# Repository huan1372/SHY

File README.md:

# SHY
Design a smartwatch whose name is SHY.
Planned feature:
Time
Heart rate
Bluetooth
Steps
Calories
Temperature
Timer

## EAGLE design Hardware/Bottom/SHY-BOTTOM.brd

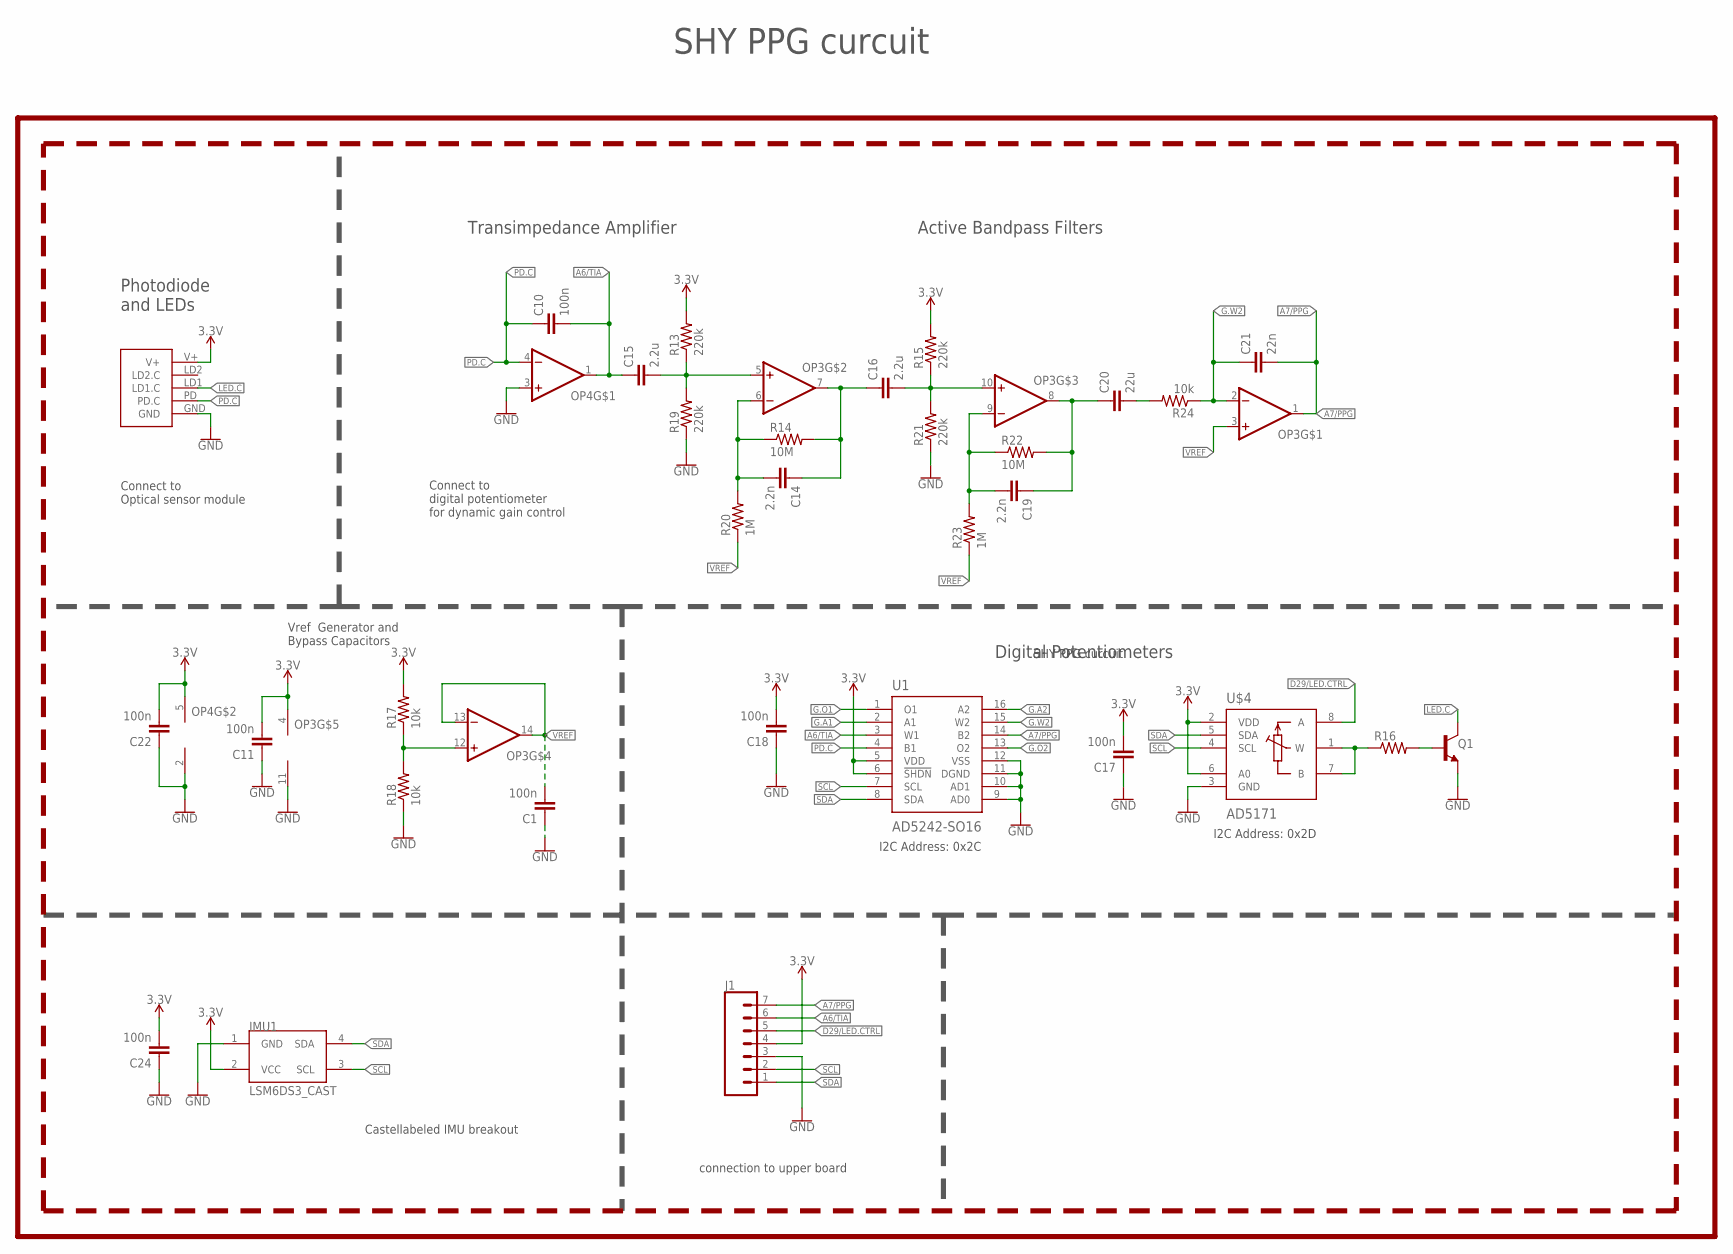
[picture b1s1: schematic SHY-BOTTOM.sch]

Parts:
C1, C10, C11, C17, C18, C22, C24: 100n; C0603
C14, C19: 2.2n; C0603
C15, C16: 2.2u; C0603
C20: 22u; C0603
C21: 22n; C0603
IMU1: LSM6DS3_CAST
J1: CONN_07-1.27MM; 1X07_1.27MM
LOGO1: REVISION.A; REV.A
LOGO2: LINNES.LAB.LOGO
OP3: OP-QUAD-SO14; SO14
OP4: OP-SINGLEOT; SOT23-5
Q1: NPN-GENERIC; SOT23-3
R13, R15, R19, R21: 220k; R0603
R14, R22: 10M; R0603
R16: RESISTOR0603; R0603
R17, R18: 10k; R0402
R20, R23: 1M; R0603
R24: 10k; R0603
U1: AD5242-SO16; SO16
U$3: PPG.MODULE.2
U$4: AD5171; SOT-23-8

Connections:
3.3V: C11.2, C17.2, C18.2, C22.2, C24.2, IMU1.2 (VCC), J1.4, OP3.4 (V+), OP4.5 (V+), R13.2, R15.2, R17.2, U1.5 (VDD), U1.6 (!SHDN), U$3.V+, U$4.2 (VDD), U$4.6 (A0)
A6/TIA: C10.2, C15.1, J1.6, OP4.1 (OUT), U1.3 (W1)
A7/PPG: C21.2, J1.7, OP3.1 (OUT), U1.14 (B2)
D29/LED.CTRL: J1.5, U$4.8 (A)
G.A1: U1.2 (A1)
G.A2: U1.16 (A2)
G.O1: U1.1 (O1)
G.O2: U1.13 (O2)
G.W2: C21.1, OP3.2 (-IN), R24.1, U1.15 (W2)
GND: C1.1, C11.1, C17.1, C18.1, C22.1, C24.1, IMU1.1 (GND), J1.3, OP3.11 (V-), OP4.2 (V-), OP4.3 (+IN), Q1.2 (E), R18.1, R19.1, R21.1, U1.9 (AD0), U1.10 (AD1), U1.11 (DGND), U1.12 (VSS), U$3.GND, U$4.3 (GND)
LED.C: Q1.3 (C), U$3.LD1 (LD1.C)
unnamed: Q1.1 (B), R16.2
unnamed: R16.1, U$4.1 (W), U$4.7 (B)
unnamed: OP3.12 (+IN), R17.1, R18.2
unnamed: C15.2, OP3.5 (+IN), R13.1, R19.2
unnamed: C14.2, OP3.6 (-IN), R14.1, R20.2
unnamed: C14.1, C16.1, OP3.7 (OUT), R14.2
unnamed: C16.2, OP3.10 (+IN), R15.1, R21.2
unnamed: C19.2, OP3.9 (-IN), R22.1, R23.2
unnamed: C19.1, C20.1, OP3.8 (OUT), R22.2
unnamed: C20.2, R24.2
PD.C: C10.1, OP4.4 (-IN), U1.4 (B1), U$3.PD (PD.C)
SCL: IMU1.3 (SCL), J1.2, U1.7 (SCL), U$4.4 (SCL)
SDA: IMU1.4 (SDA), J1.1, U1.8 (SDA), U$4.5 (SDA)
VREF: C1.2, OP3.3 (+IN), OP3.13 (-IN), OP3.14 (OUT), R20.1, R23.1

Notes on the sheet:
Photodiode and LEDs
Active Bandpass Filters
Digital Potentiometers
Transimpedance Amplifier
I2C Address: 0x2C
I2C Address: 0x2D
Connect to Optical sensor module
Connect to digital potentiometer for dynamic gain control
connection to upper board
Castellabeled IMU breakout
Vref Generator and Bypass Capacitors
SHY PPG curcuit

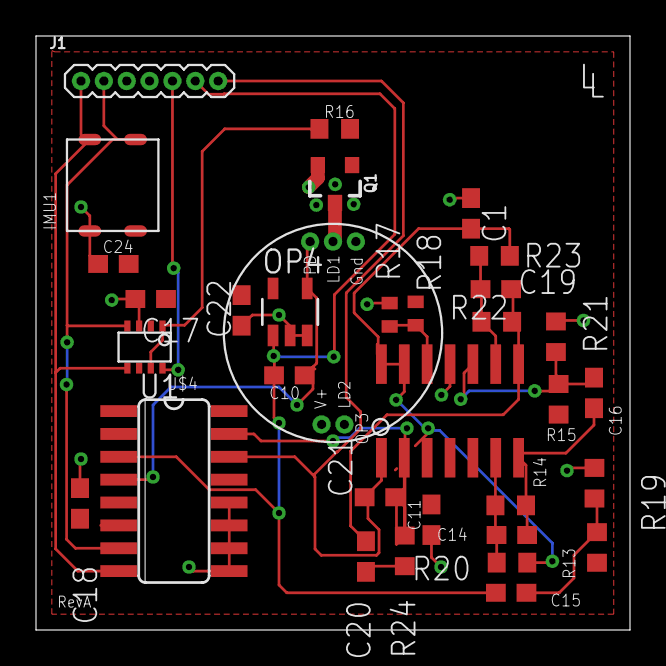
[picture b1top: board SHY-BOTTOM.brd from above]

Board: 2 copper layers, 33.0 x 33.0 mm, 35 parts (0 on the bottom side), 21 nets.

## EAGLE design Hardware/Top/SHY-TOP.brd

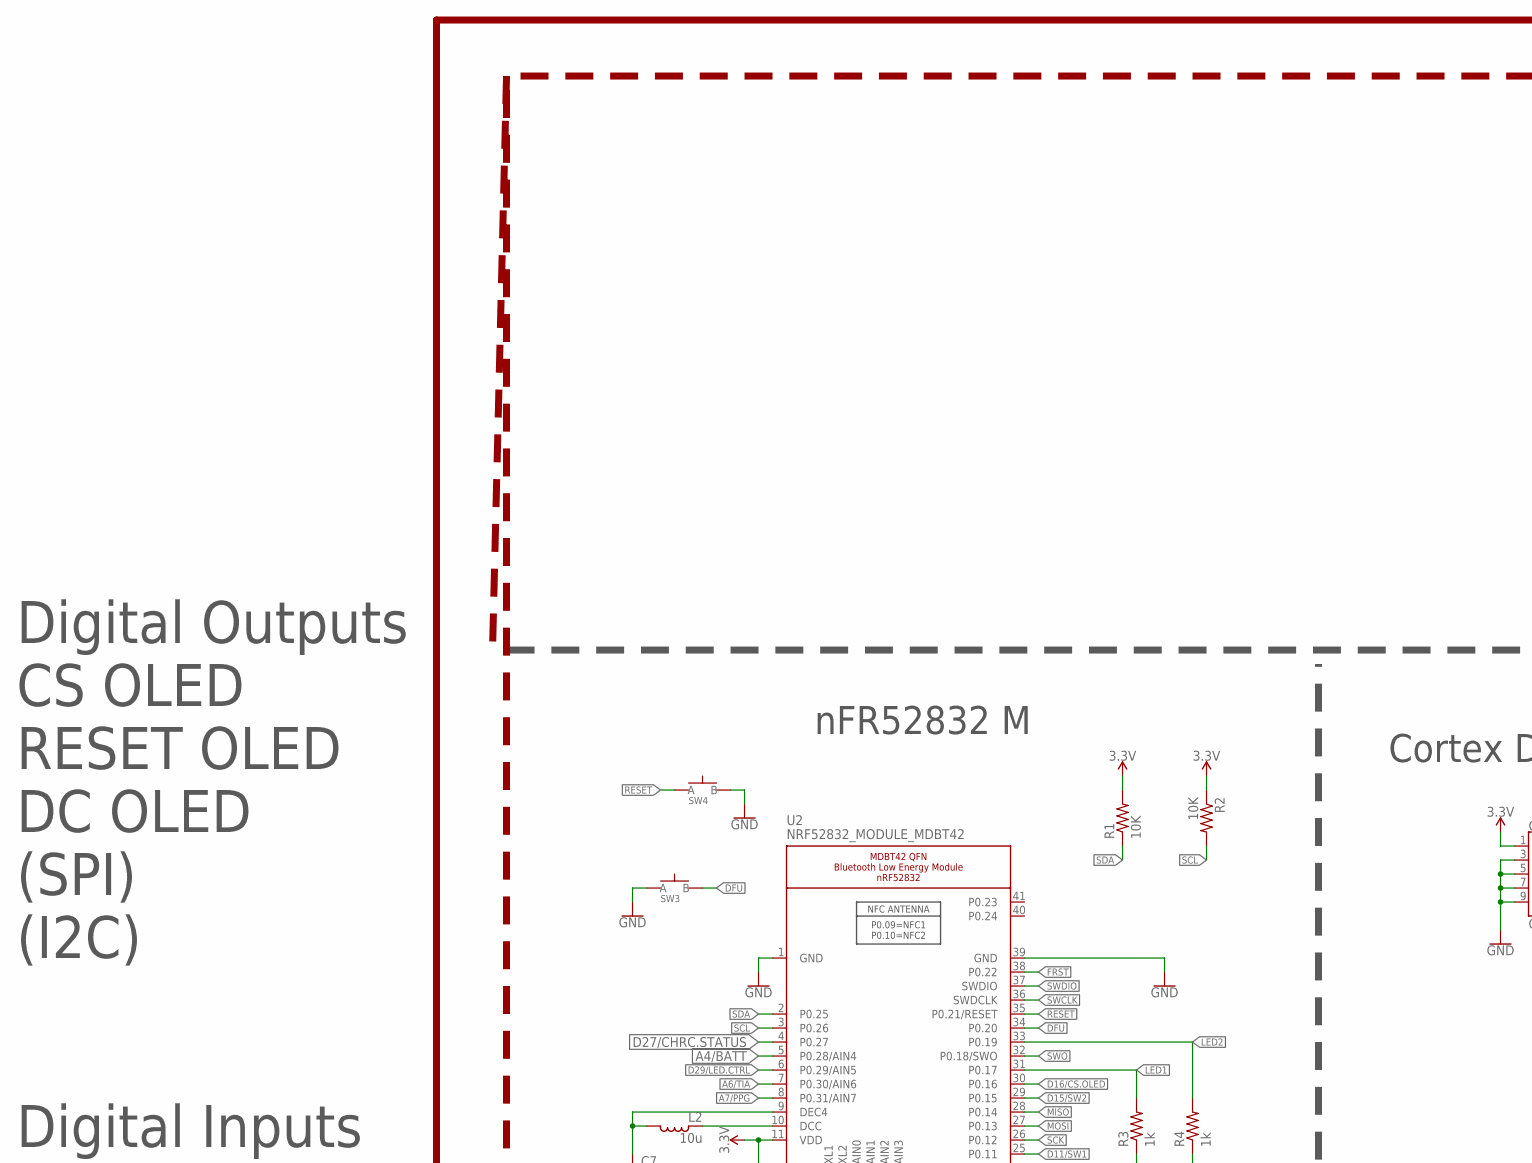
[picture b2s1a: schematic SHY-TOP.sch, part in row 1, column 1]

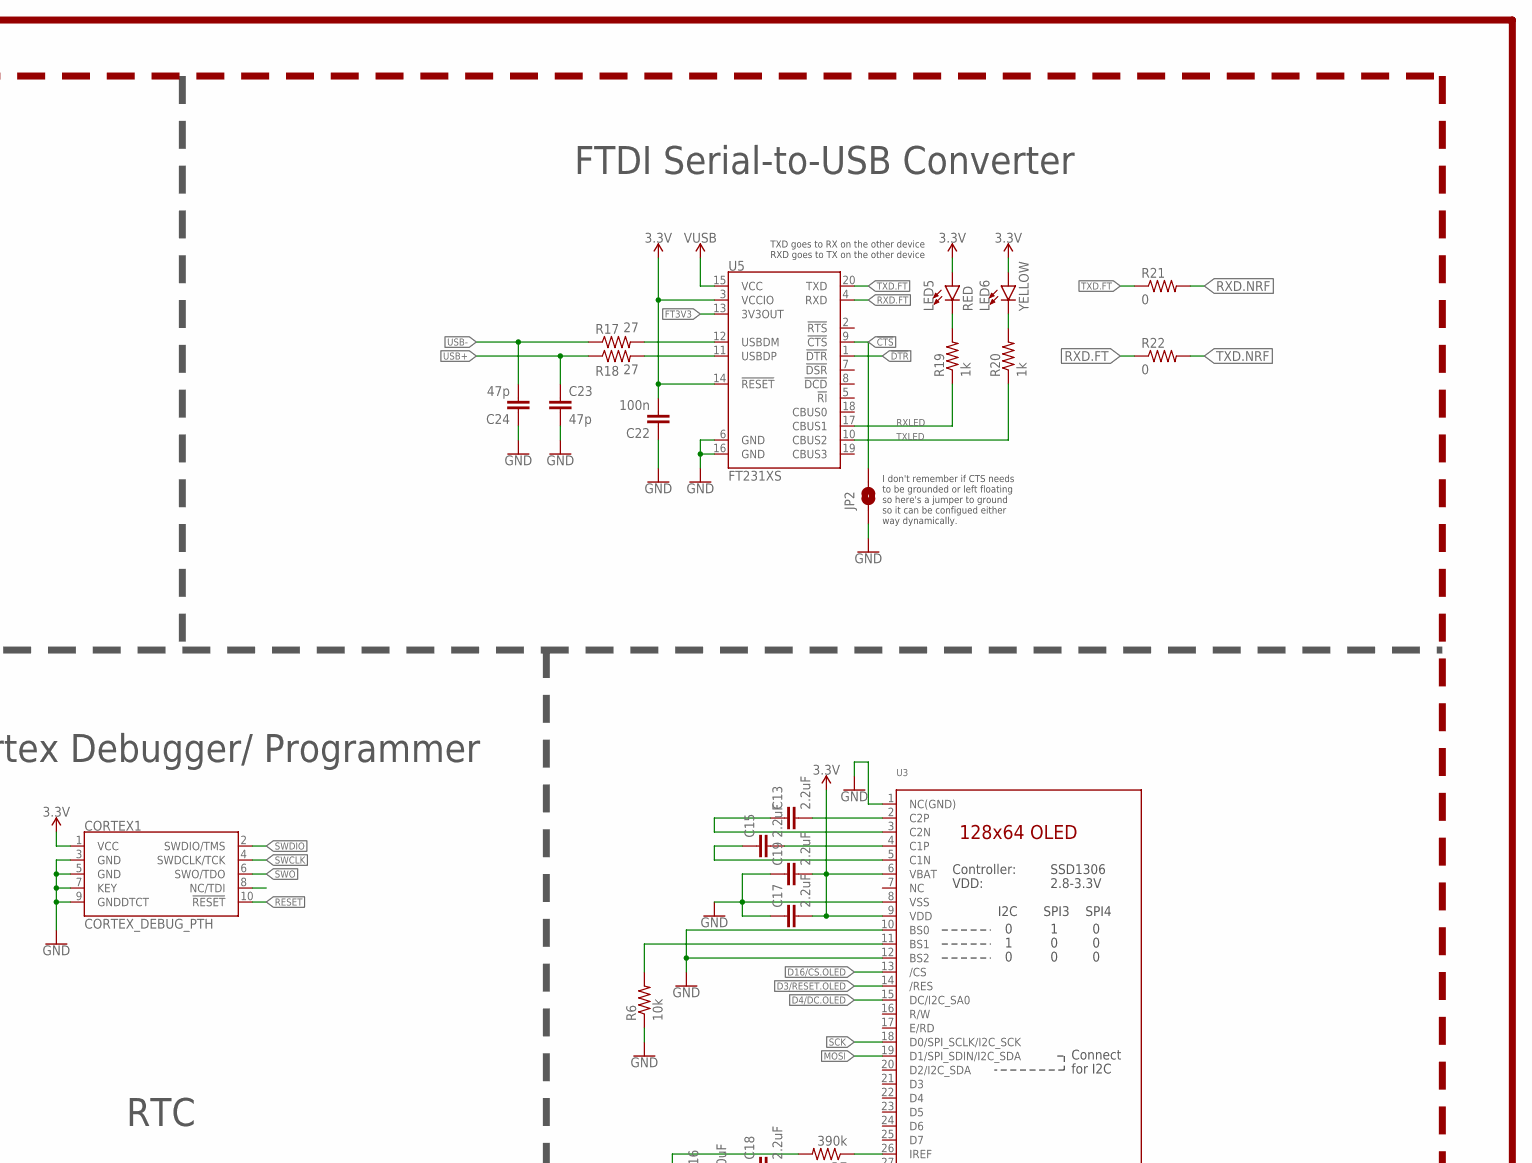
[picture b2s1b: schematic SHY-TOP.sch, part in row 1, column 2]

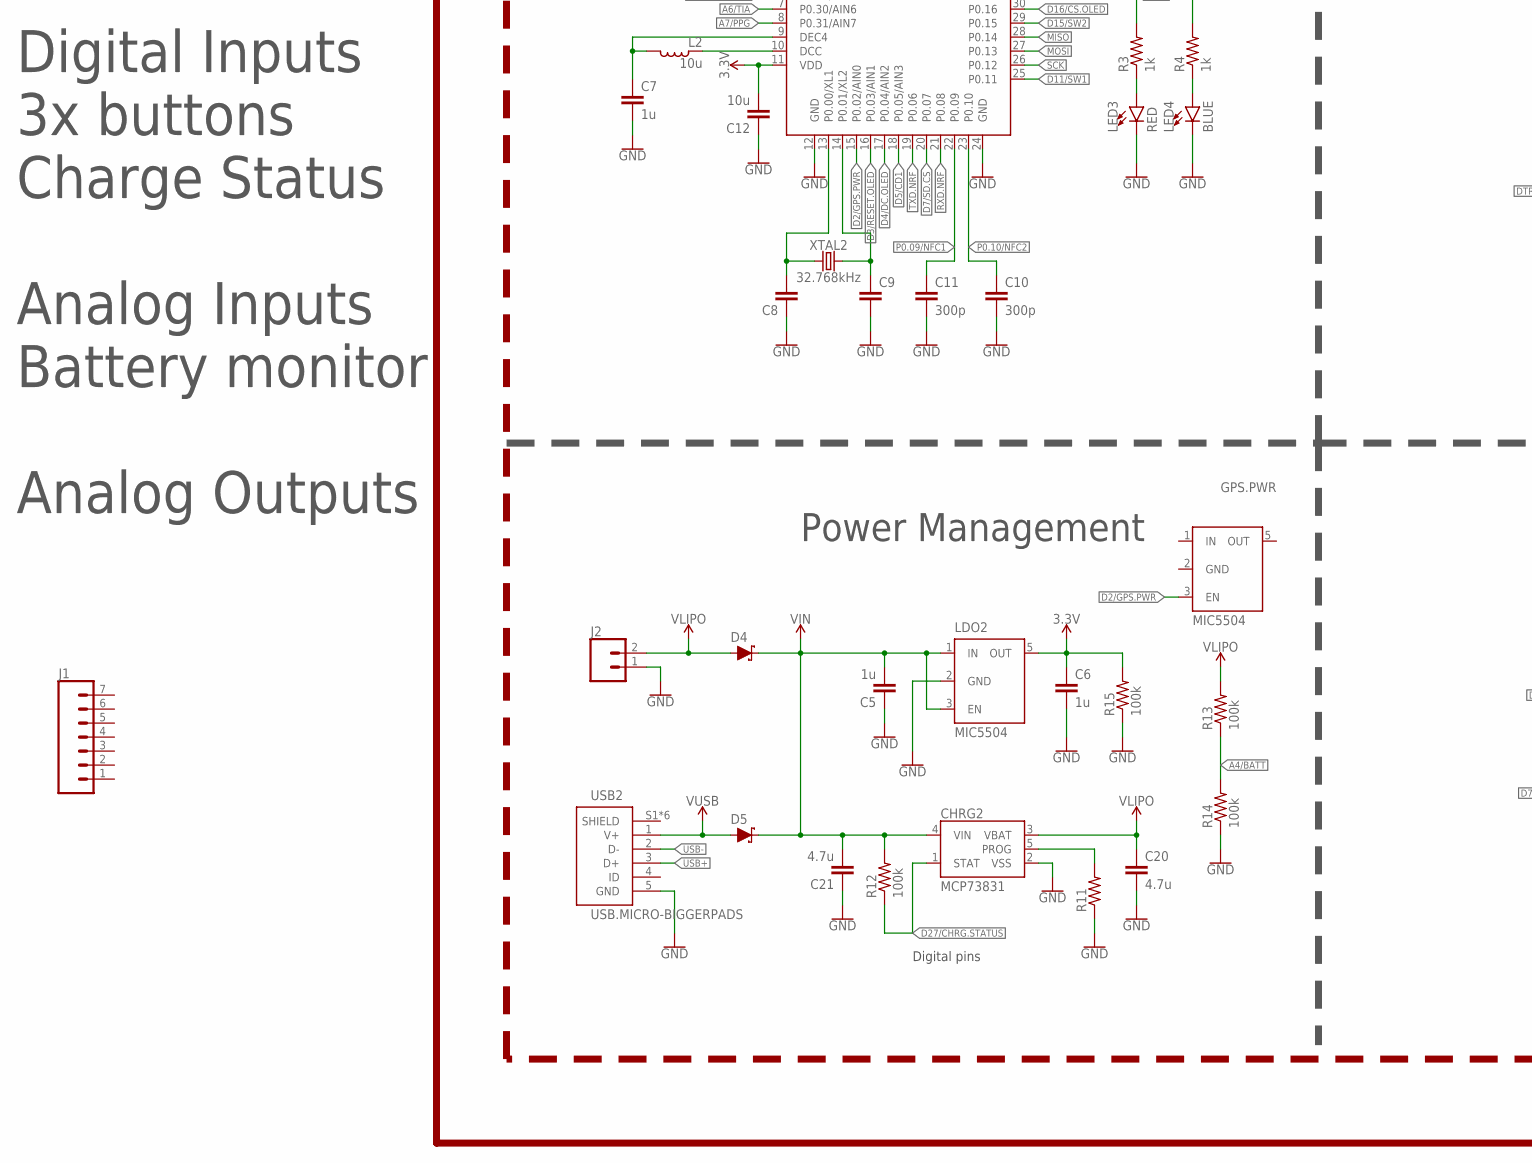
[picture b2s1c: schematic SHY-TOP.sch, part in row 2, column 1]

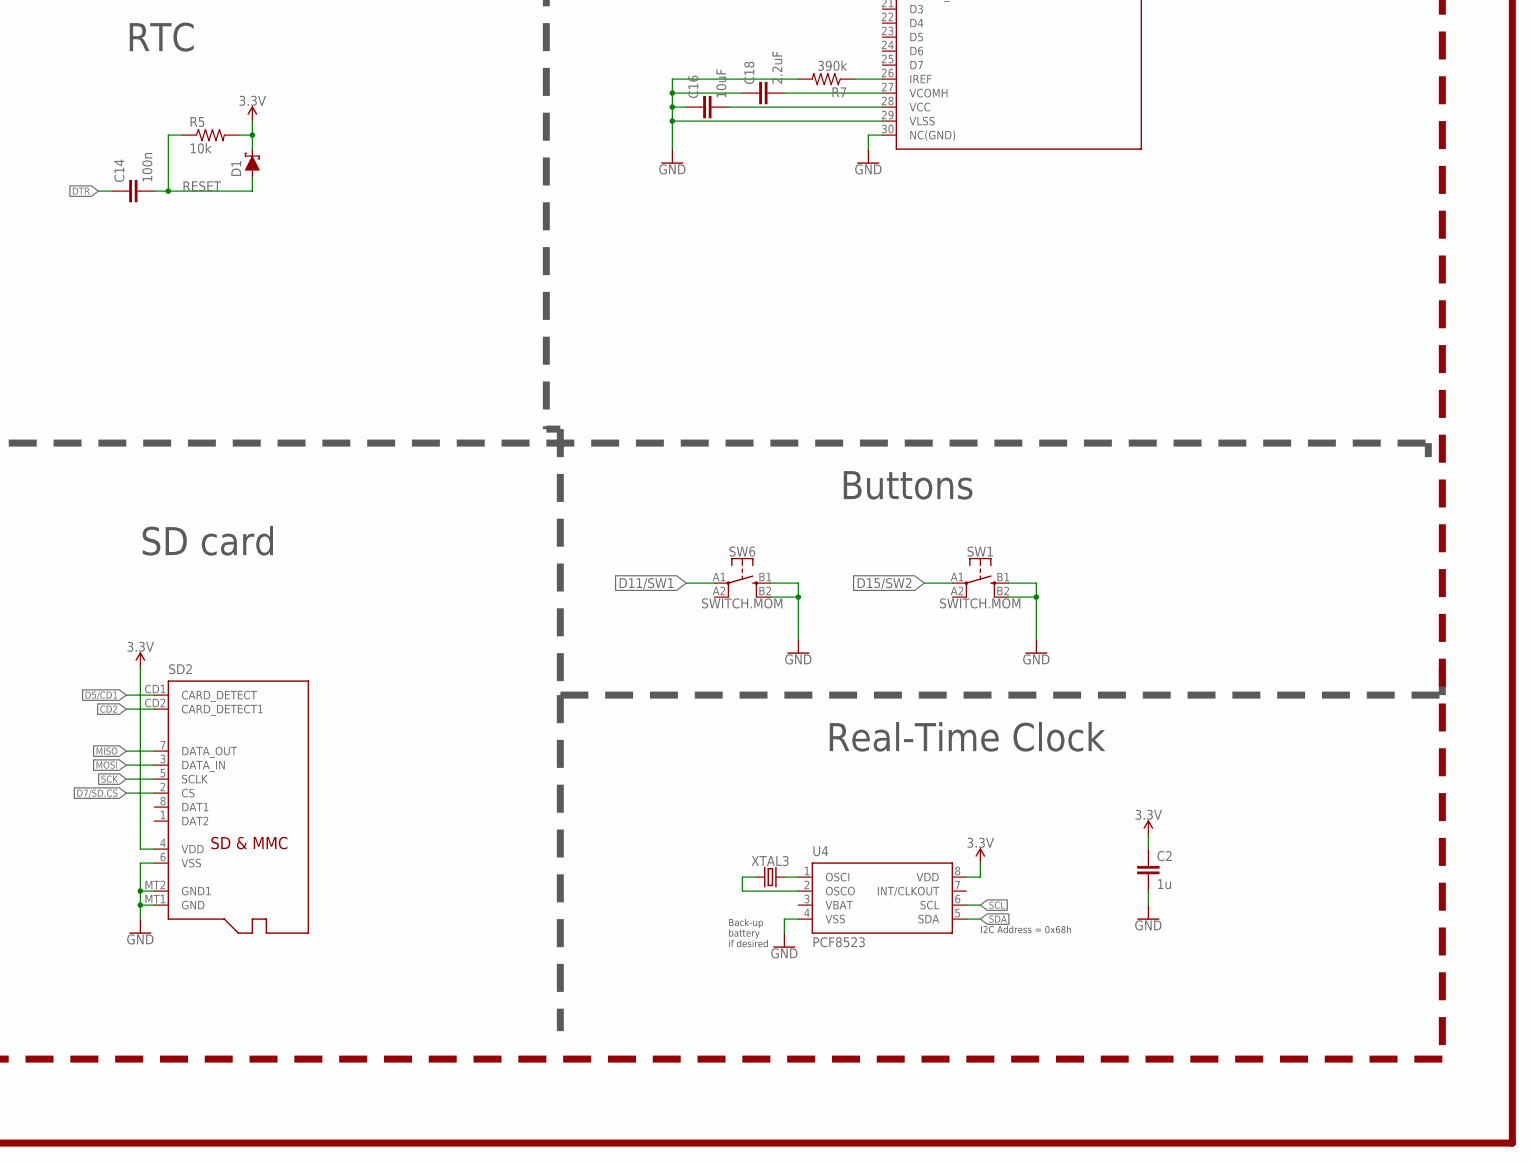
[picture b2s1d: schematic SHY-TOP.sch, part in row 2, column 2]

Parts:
C2, C5, C6, C7: 1u; C0603
C8, C9: CAPACITOR0603; C0603
C10, C11: 300p; C0603
C12: 10u; C0805
C13, C15, C17, C18, C19: 2.2uF; C0402
C14, C22: 100n; C0603
C16: 10uF; C0603
C20, C21: 4.7u; C0603
C23, C24: 47p; C0603
CHRG2: MCP73831; SOT23-5
CORTEX1: CORTEX_DEBUG_PTH; 2X5-PTH-1.27MM
D1, D4, D5: SCHOTTKY-USC; USC
GPS.PWR: MIC5504; SOT23-5
J1: CONN_07; 1X07
J2: CONN_02; 1X02
JP2: JUMPER-SMT_2_NO_SILK; SMT-JUMPER_2_NO_SILK
L2: 10u; L0603
LDO2: MIC5504; SOT23-5
LED3, LED5: RED; LED-0603
LED4: BLUE; LED-0603
LED6: YELLOW; LED-0603
R1, R2: 10K; R0603
R3, R4, R19, R20: 1k; R0603
R5, R6: 10k; R0603
R7: 390k; R0603
R11: RESISTOR0603; R0603
R12, R13, R14, R15: 100k; R0603
R17, R18: 27; R0603
R21, R22: 0; R0603
SD2: MICROSD
SW1, SW6: SWITCH.MOM; TACTILE_SWITCH_SMD_6.2MM_TALL
SW3, SW4: SPST-PTS830GG140-COPY.1-3; BUTTON-GULLWING
U2: NRF52832_MODULE_MDBT42; BLE_MODULE_RAYTAC_MDBT42
U3: DISP_OLED_UG-2864HSWEG01-NO-WRAPAROUND; UG-2864HSWEG01_0.96IN_NO-WRAPAROUND
U4: PCF8523; SO8; DIGIKEY 568-5306-1-ND
U5: FT231XS; SSOP20_L
USB2: USB.MICRO-BIGGERPADS; USB-MICRO-01.BIGGERPADS
XTAL2: 32.768kHz; 2-SMD.NOLEAD.2.0MMTO1.2MM
XTAL3: 32.7680kHz; 2-SMD.NOLEAD.2.0MMTO1.2MM

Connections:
3.3V: C2.1, C6.1, C12.2, C17.2, C19.2, C22.2, CORTEX1.1 (VCC), D1.- (C), LDO2.5 (OUT), LED5.A, LED6.A, R1.2, R2.1, R5.2, R15.2, SD2.4 (VDD), U2.11 (VDD), U3.6 (VBAT), U3.9 (VDD), U4.8 (VDD), U5.3 (VCCIO), U5.14 (!RESET)
!CTS: JP2.2, U5.9 (!CTS)
!DTR: U5.1 (!DTR)
A4/BATT: R13.1, R14.2, U2.5 (P0.28/AIN4)
A6/TIA: U2.7 (P0.30/AIN6)
A7/PPG: U2.8 (P0.31/AIN7)
CD2: SD2.CD2 (CARD_DETECT1)
D2/GPS.PWR: GPS.PWR.3 (EN), U2.15 (P0.02/AIN0)
D3/RESET.OLED: U2.16 (P0.03/AIN1), U3.14 (/RES)
D4/DC.OLED: U2.17 (P0.04/AIN2), U3.15 (DC/I2C_SA0)
D5/CD1: SD2.CD1 (CARD_DETECT), U2.18 (P0.05/AIN3)
D7/SD.CS: SD2.2 (CS), U2.20 (P0.07)
D11/SW1: SW6.A1 (1), U2.25 (P0.11)
D15/SW2: SW1.A1 (1), U2.29 (P0.15)
D16/CS.OLED: U2.30 (P0.16), U3.13 (/CS)
D27/CHRC.STATUS: U2.4 (P0.27)
D27/CHRG.STATUS: CHRG2.1 (STAT), R12.1
D29/LED.CTRL: U2.6 (P0.29/AIN5)
DFU: SW3.3 (B), U2.34 (P0.20)
DTR: C14.1
FRST: U2.38 (P0.22)
FT3V3: U5.13 (3V3OUT)
GND: C2.2, C5.1, C6.2, C7.2, C8.1, C9.2, C10.2, C11.2, C12.1, C16.1, C17.1, C18.1, C19.1, C20.2, C21.1, C22.1, C23.2, C24.1, CHRG2.2 (VSS), CORTEX1.3 (GND), CORTEX1.5 (GND), CORTEX1.7 (KEY), CORTEX1.9 (GNDDTCT), J2.1, JP2.1, LDO2.2 (GND), LED3.C, LED4.C, R6.1, R7.2, R11.1, R14.1, R15.1, SD2.6 (VSS), SD2.MT1 (GND), SD2.MT2 (GND1), SW1.B1 (3), SW1.B2 (4), SW3.1 (A), SW4.3 (B), SW6.B1 (3), SW6.B2 (4), U2.1 (GND), U2.12 (GND), U2.24 (GND), U2.39 (GND), U3.1 (NC(GND)), U3.8 (VSS), U3.10 (BS0), U3.12 (BS2), U3.29 (VLSS), U3.30 (NC(GND)), U4.4 (VSS), U5.6 (GND), U5.16 (GND), USB2.5 (GND)
LED1: R3.2, U2.31 (P0.17)
LED2: R4.2, U2.33 (P0.19)
MISO: SD2.7 (DATA_OUT), U2.28 (P0.14)
MOSI: SD2.3 (DATA_IN), U2.27 (P0.13), U3.19 (D1/SPI_SDIN/I2C_SDA)
unnamed: R6.2, U3.11 (BS1)
unnamed: R7.1, U3.26 (IREF)
unnamed: C13.2, U3.2 (C2P)
unnamed: C8.2, U2.13 (P0.00/XL1), XTAL2.P$1 (1)
unnamed: C13.1, U3.3 (C2N)
unnamed: C9.1, U2.14 (P0.01/XL2), XTAL2.P$2 (2)
unnamed: C15.2, U3.4 (C1P)
unnamed: C15.1, U3.5 (C1N)
unnamed: LED3.A, R3.1
unnamed: LED4.A, R4.1
unnamed: L2.1, U2.10 (DCC)
unnamed: C7.1, L2.2, U2.9 (DEC4)
unnamed: C16.2, U3.28 (VCC)
unnamed: C18.2, U3.27 (VCOMH)
unnamed: CHRG2.5 (PROG), R11.2
unnamed: U4.2 (OSCO), XTAL3.P$1 (1)
unnamed: U4.1 (OSCI), XTAL3.P$2 (2)
unnamed: R17.2, U5.12 (USBDM)
unnamed: R18.2, U5.11 (USBDP)
unnamed: LED5.C, R19.2
unnamed: LED6.C, R20.2
P0.09/NFC1: C11.1, U2.22 (P0.09)
P0.10/NFC2: C10.1, U2.23 (P0.10)
RESET: C14.2, CORTEX1.10 (!RESET), D1.+ (A), R5.1, SW4.1 (A), U2.35 (P0.21/RESET)
RXD.FT: R22.1, U5.4 (RXD)
RXD.NRF: R21.2, U2.21 (P0.08)
RXLED: R19.1, U5.17 (CBUS1)
SCK: SD2.5 (SCLK), U2.26 (P0.12), U3.18 (D0/SPI_SCLK/I2C_SCK)
SCL: R2.2, U2.3 (P0.26), U4.6 (SCL)
SDA: R1.1, U2.2 (P0.25), U4.5 (SDA)
SWCLK: CORTEX1.4 (SWDCLK/TCK), U2.36 (SWDCLK)
SWDIO: CORTEX1.2 (SWDIO/TMS), U2.37 (SWDIO)
SWO: CORTEX1.6 (SWO/TDO), U2.32 (P0.18/SWO)
TXD.FT: U5.20 (TXD)
TXD.NRF: R22.2, U2.19 (P0.06)
TXLED: R20.1, U5.10 (CBUS2)
USB+: C23.1, R18.1, USB2.3 (D+)
USB-: C24.2, R17.1, USB2.2 (D-)
VBAT: U4.3 (VBAT)
VIN: C5.2, C21.2, CHRG2.4 (VIN), D4.- (C), D5.- (C), LDO2.1 (IN), LDO2.3 (EN), R12.2
VLIPO: C20.1, CHRG2.3 (VBAT), D4.+ (A), J2.2, R13.2
V_USB: D5.+ (A), U5.15 (VCC), USB2.1 (V+)

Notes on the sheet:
I2C Address = 0x68h
Back-up battery if desired
nFR52832 M
Cortex Debugger/ Programmer
RTC
Power Management
SD card
Buttons
Real-Time Clock
Digital Outputs CS OLED RESET OLED DC OLED (SPI) (I2C) Digital Inputs 3x buttons Charge Status Analog Inputs Battery monitor Analog Outputs
TXD goes to RX on the other device RXD goes to TX on the other device
I don't remember if CTS needs to be grounded or left floating so here's a jumper to ground so it can be configued either way dynamically.
FTDI Serial-to-USB Converter
Digital pins

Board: 2 copper layers, 66 parts (2 on the bottom side), 58 nets, no tracks yet.

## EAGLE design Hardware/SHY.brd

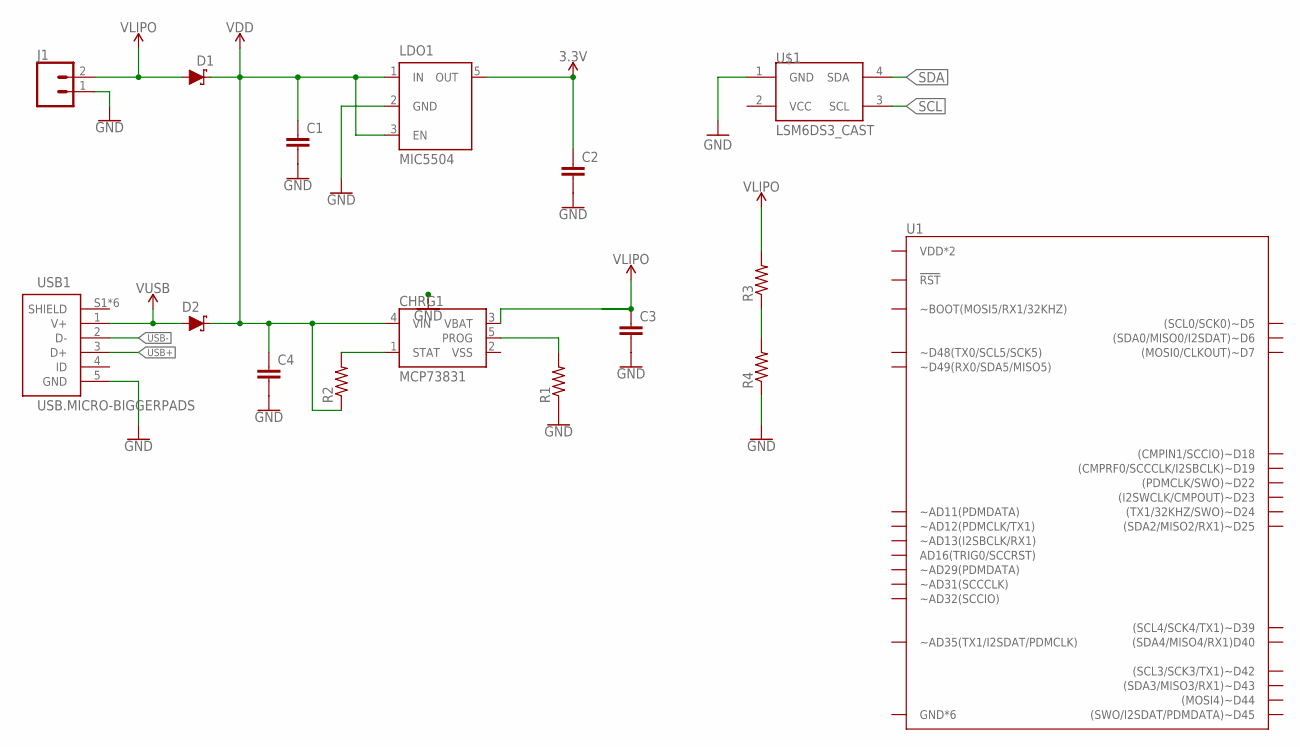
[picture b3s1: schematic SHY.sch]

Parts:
C1, C2, C3, C4: CAPACITOR0603; C0603
CHRG1: MCP73831; SOT23-5
D1, D2: SCHOTTKY-USC; USC
J1: CONN_02; 1X02
LDO1: MIC5504; SOT23-5
R1, R2, R3, R4: RESISTOR0603; R0603
U1: ARTEMIS.CAST; ARTEMIS_CAST
U$1: LSM6DS3_CAST
USB1: USB.MICRO-BIGGERPADS; USB-MICRO-01.BIGGERPADS

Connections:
3.3V: C2.1, LDO1.5 (OUT)
GND: C1.2, C2.2, C3.2, C4.2, J1.1, LDO1.2 (GND), R1.1, R4.1, U$1.1 (GND), USB1.5 (GND)
unnamed: R3.1, R4.2
unnamed: CHRG1.1 (STAT), R2.2
unnamed: CHRG1.5 (PROG), R1.2
SCL: U$1.3 (SCL)
SDA: U$1.4 (SDA)
USB+: USB1.3 (D+)
USB-: USB1.2 (D-)
VDD: C1.1, C4.1, CHRG1.4 (VIN), D1.- (C), D2.- (C), LDO1.1 (IN), LDO1.3 (EN), R2.1
VLIPO: C3.1, CHRG1.3 (VBAT), D1.+ (A), J1.2, R3.2
VSS: CHRG1.2 (VSS)
V_USB: D2.+ (A), USB1.1 (V+)

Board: 2 copper layers, 16 parts (0 on the bottom side), 8 nets, no tracks yet.

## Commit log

2020-02-02 Add the Firmware: the sofware and Hardware
2020-02-09 add few components
2020-02-12 Add 3.3v and gnd
2020-02-17 Add some resistors and compacitors
2020-05-28 Edit README
2020-05-28 Add a document with explanation of smartwatch's features
2020-06-02 revise need
2020-06-04 Add folder for bottom design
2020-06-04 Folder for Top design
2020-06-04 add PPG
2020-06-04 gitignore file
2020-06-04 remove
2020-06-05 Add top board
2020-06-05 ignore file
2020-06-05 Add content for bottom board
2020-06-11 bottom board design
2020-06-11 top board design
2020-06-23 update software design
2020-06-24 update D2/pin15 connection
2020-06-25 till 53:17
2020-06-25 finish bottom board
